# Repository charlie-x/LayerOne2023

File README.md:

# LayerOne2023

# Hardware

PIC16F1455

WS2812B/SK6812

# Software Needed

Microchip MPLAB 6.10

  https://www.microchip.com/en-us/tools-resources/develop/mplab-x-ide
  
XC8 2.41

  https://www.microchip.com/en-us/tools-resources/develop/mplab-xc-compilers/downloads-documentation#XC8

# DFU mode bootloader

 Badge has a DFU loader, hold the button down while plugging in USB should appear as device
 In Windows use ZADIG https://github.com/pbatard/libwdi/releases/download/v1.5.0/zadig-2.8.exe to change the driver to WinUSB device ID will be 1209:2002
 Modified Bootloader code is at https://github.com/charlie-x/PIC16F1455_Bootloader full fork https://github.com/charlie-x/PIC16F1455_Bootloader with tools
 
# dfu-utils to upload to badge
 
 convert hex file from Bootloader MPLAB project ( must use the HTxxxxxx_BootLoader version )
 
 get 454hex2dfu here https://github.com/charlie-x/PIC16F1-USB-DFU-Bootloader/tree/master/tools 
 
  454hex2dfu input.hex OKBBPIC_firmware.production.dfu
 
 put badge in DFU mode by holding button down and plugging into usb. (only when L1 bootloader is installed, if its overwritten you have to reinstall it with a PIC programmer like the pickkit3)
 
  dfu-util  -l -D OKBBPIC_firmware.production.dfu -R
 
# Optional Programmer

Pickit 3 or better , Pickit 2 supports CU with 3rd party sofware ,3 or 4 is recommended.

# badge competition

there is a very partial rubberducky 2.0 script commented out in the code, whoever makes it run duckyscript first, wins the single prize. claim with charliex, mmca or datagram.

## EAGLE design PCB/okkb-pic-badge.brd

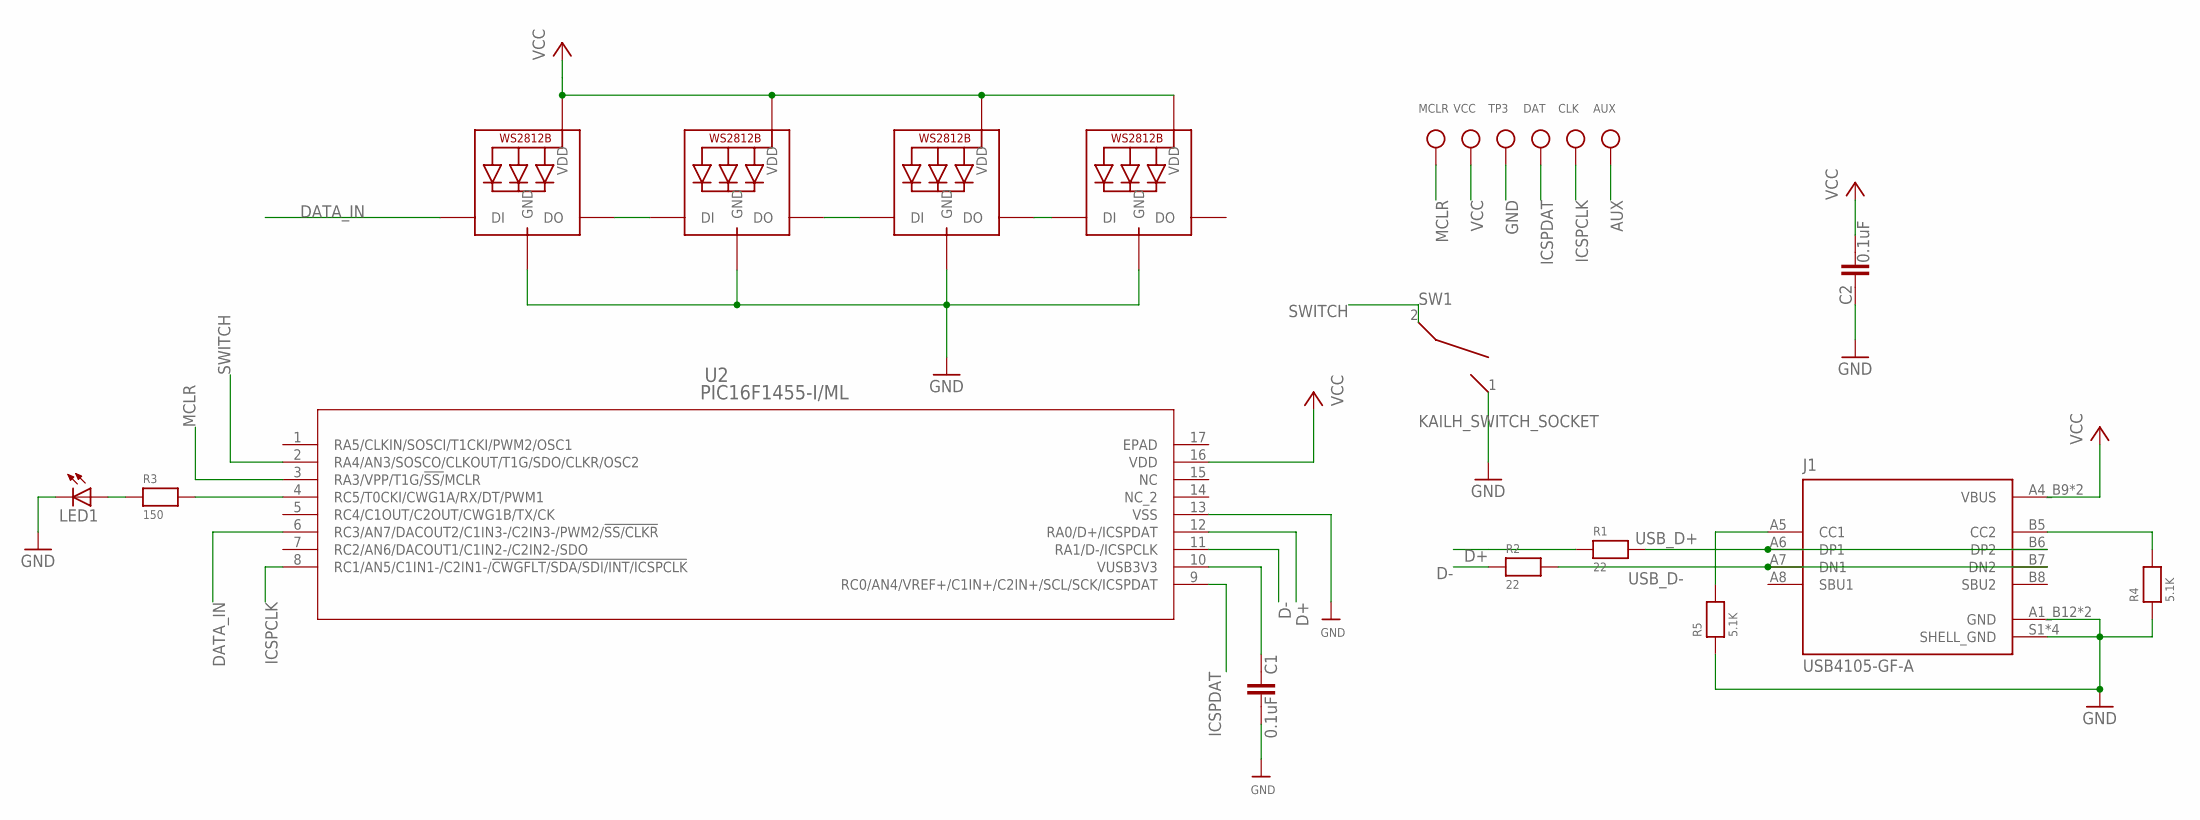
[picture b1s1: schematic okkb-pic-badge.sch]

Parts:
AUX: TESTPOINTROUND1MM; TESTPOINT_ROUND_1MM
C1, C2: 0.1uF; C0805
CLK: TESTPOINTROUND1MM; TESTPOINT_ROUND_1MM
DAT: TESTPOINTROUND1MM; TESTPOINT_ROUND_1MM
J1: USB4105-GF-A; GCT_USB4105-GF-A
LED1: LEDCHIPLED_1206; CHIPLED_1206
LED2, LED3, LED4, LED5: WS2812B3535; LED3535
MCLR: TESTPOINTROUND1MM; TESTPOINT_ROUND_1MM
R1, R2: 22; 0805
R3: 150; _0805
R4, R5: 5.1K; 0805
SW1: KAILH_SWITCH_SOCKET; SWITCH_SOCKET
TP3: TESTPOINTROUND1MM; TESTPOINT_ROUND_1MM
U2: PIC16F1455-I/ML; QFN16_4X4MC
VCC: TESTPOINTROUND1MM; TESTPOINT_ROUND_1MM

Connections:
AUX: AUX.P$1
D+: R1.1, U2.12 (RA0/D+/ICSPDAT)
D-: R2.1, U2.11 (RA1/D-/ICSPCLK)
DATA_IN: LED2.1 (DI), U2.6 (RC3/AN7/DACOUT2/C1IN3-/C2IN3-/PWM2/!SS/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)
GND: C1.2, C2.1, J1.A1_B12 (GND), J1.B1_A12 (GND), J1.S1 (SHELL_GND), J1.S2 (SHELL_GND), J1.S3 (SHELL_GND), J1.S4 (SHELL_GND), LED1.C, LED2.4 (GND), LED3.4 (GND), LED4.4 (GND), LED5.4 (GND), R4.1, R5.1, SW1.1 (2), TP3.P$1, U2.13 (VSS)
ICSPCLK: CLK.P$1, U2.8 (RC1/AN5/C1IN1-/C2IN1-/!CWGFLT/SDA/SDI/I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)
ICSPDAT: DAT.P$1, U2.9 (RC0/AN4/VREF+/C1IN+/C2IN+/SCL/SCK/ICSPD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)
MCLR: MCLR.P$1, U2.3 (RA3/VPP/T1G/!SS/!MCLR)
unnamed: R3.2, U2.4 (RC5/T0CKI/CWG1A/RX/DT/PWM1)
unnamed: LED1.A, R3.1
unnamed: C1.1, U2.10 (VUSB3V3)
unnamed: LED2.3 (DO), LED3.1 (DI)
unnamed: LED3.3 (DO), LED4.1 (DI)
unnamed: LED4.3 (DO), LED5.1 (DI)
unnamed: J1.A5 (CC1), R5.2
unnamed: J1.B5 (CC2), R4.2
SWITCH: SW1.2 (1), U2.2 (RA4/AN3/SOSCO/CLKOUT/T1G/SDO/CLKR/OSC2)
USB_D+: J1.A6 (DP1), J1.B6 (DP2), R1.2
USB_D-: J1.A7 (DN1), J1.B7 (DN2), R2.2
VCC: C2.2, J1.A4_B9 (VBUS), J1.B4_A9 (VBUS), LED2.2 (VDD), LED3.2 (VDD), LED4.2 (VDD), LED5.2 (VDD), U2.16 (VDD), VCC.P$1

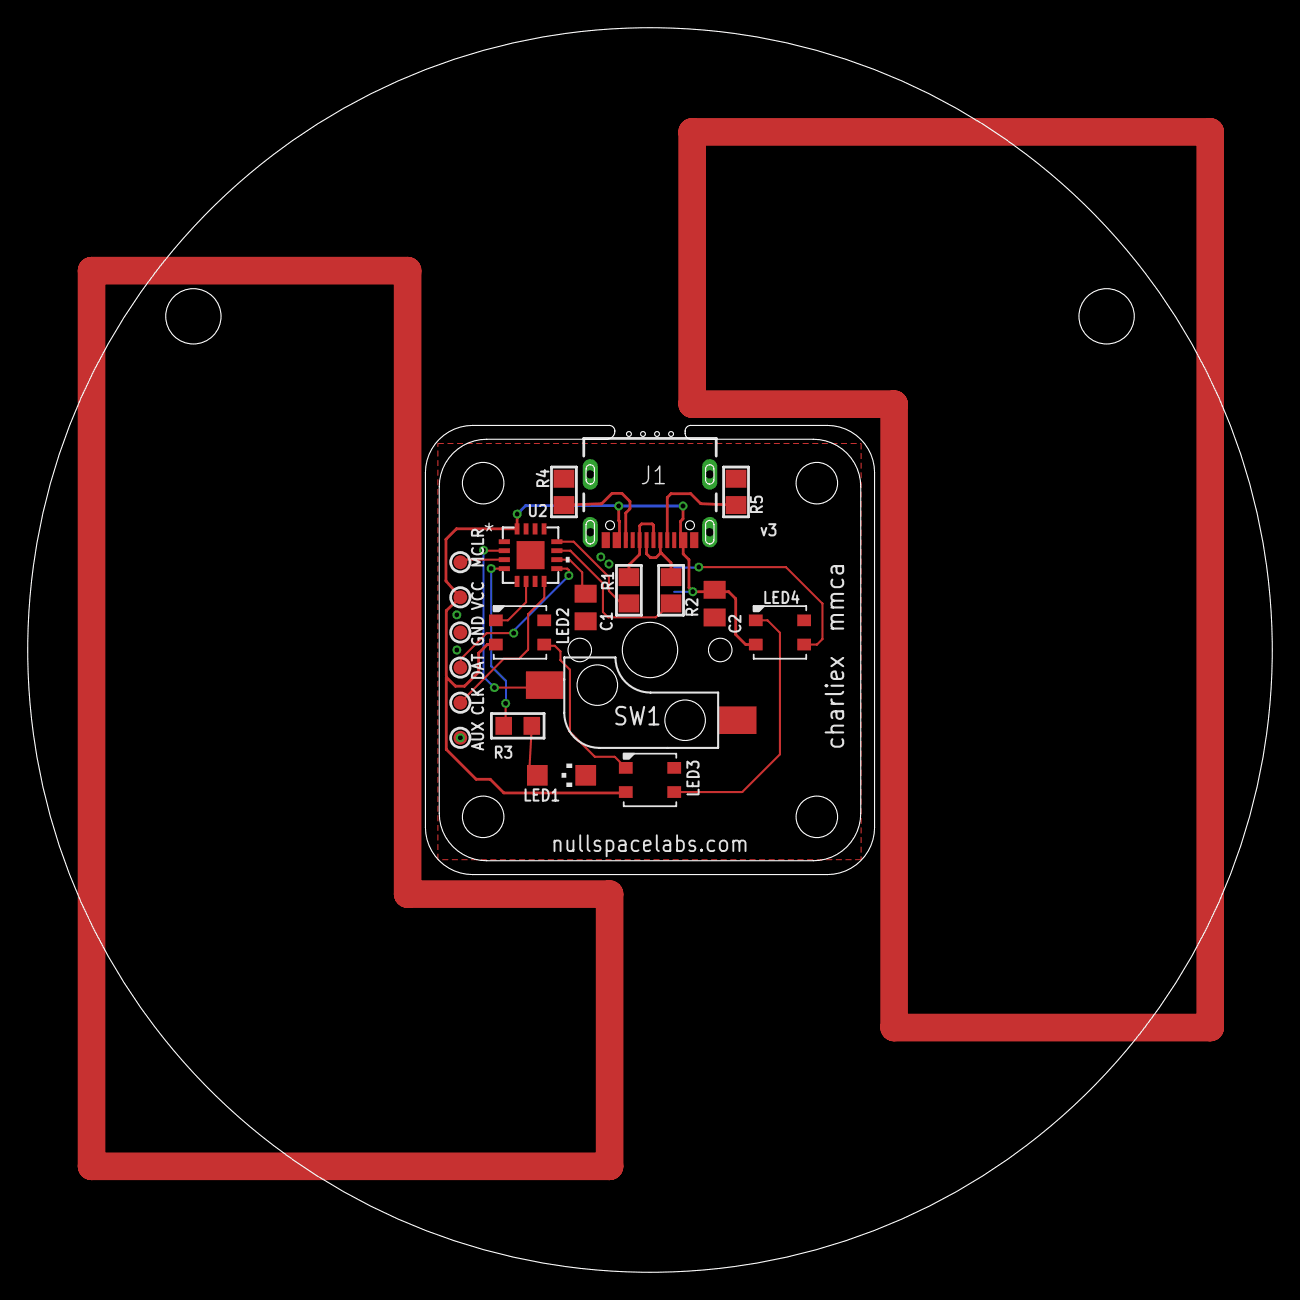
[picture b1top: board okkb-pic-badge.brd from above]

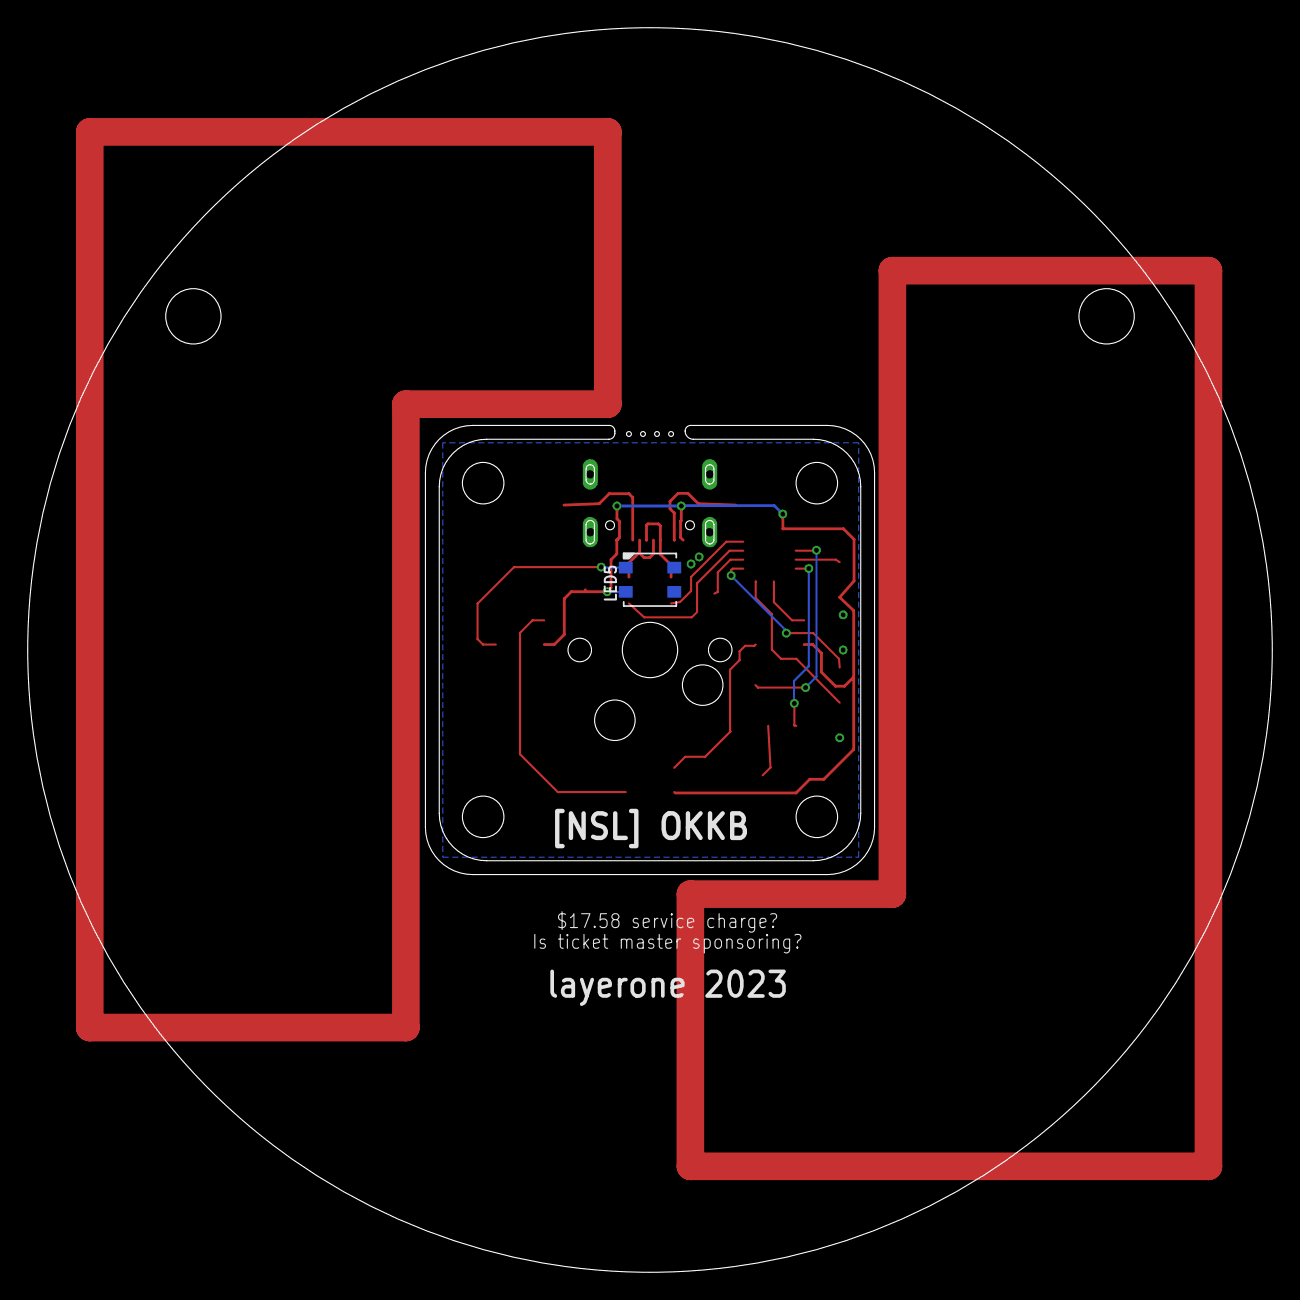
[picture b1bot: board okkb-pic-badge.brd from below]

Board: 2 copper layers, 90.0 x 90.0 mm, 21 parts (2 on the bottom side), 19 nets.

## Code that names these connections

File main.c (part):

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#pragma config FOSC = INTOSC    // Oscillator Selection Bits (INTOSC oscillator: I/O function on CLKIN pin)
#pragma config WDTE = OFF       // Watchdog Timer Enable (WDT disabled)
#pragma config PWRTE = OFF      // Power-up Timer Enable (PWRT disabled)
#pragma config MCLRE = OFF      // MCLR Pin Function Select (MCLR/VPP pin function is Digital Input)
#pragma config CP = OFF         // Flash Program Memory Code Protection (Program memory code protection is disabled)
#pragma config BOREN = ON       // Brown-out Reset Enable (Brown-out Reset enabled)
#pragma config CLKOUTEN = OFF   // Clock Out Enable (CLKOUT function is disabled. I/O or oscillator function on the CLKOUT pin)
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/*
    Pinouts for peripherals
 *
    #define WS2812              RC3
    #define Button              RA4 // RA4 for new version
    #define Led                 RC5
    
*/
    TRISC = 0b00010000; // Set RC3 as output (WS2812) except RA4 for Button
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
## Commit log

2023-05-25 Add files via upload
    initial commit
2023-05-25 Add files via upload
    uploaded windows dfu-utils
2023-05-25 Add files via upload
    adding eagle files
2023-05-25 Add files via upload
    case 3MF files
2023-05-25 Add files via upload
    adding datasheet
2023-05-25 Add files via upload
    OKKBB Macro editor windows version
2023-05-25 Add files via upload
    added linux/simple command line version
2023-05-26 added some extra demo code.

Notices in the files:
parts and their libraries:
microbuilder: This work is placed in the public domain, and may be freely used for commercial and non-commercial work with the following conditions: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
